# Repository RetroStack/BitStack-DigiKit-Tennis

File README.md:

# DigiKit Tennis Replica

While watching my regular YouTube channels, I saw a digital electronics kit from the 70s called Tennis from the company DigiKit, [shown on the Tech Time Traveller](https://www.youtube.com/watch?v=UqEwdttDtZE&t=2260s). This is a neat little board with a fun game that looks useful for beginners to learn digital electronics. The provided schematic had a lot of bugs and was very incorrect. 

I spent some time reverse engineering it from screenshots of the YouTube video, and the result is this board.

## Latest Files

In the "Latest" folder, you'll find the most up-to-date design files, including:

- Gerber files suitable for popular online PCB manufacturers like [PCBWay](/Latest/DigiKit_Tennis_Gerber_PCBWay.zip) and [JLCPCB](/Latest/DigiKit_Tennis_Gerber_JLCPCB.zip). Most manufacturers should be fine with either.
- A Bill of Materials (BOM) in both [CSV](/Latest/DigiKit_Tennis_BOM.csv) and [PDF](/Latest/DigiKit_Tennis_BOM.pdf) formats.
- The [full schematics](/Latest/DigiKit_Tennis_Schematics.pdf) of the board.

## How to Play

This is a simple game of Pong where the lights in the center of the board are used to indicate the path of the "ball." The goal of the game is to hit the ball back to the other player. When the player on the receiving end misses the ball, a point is given to the one sending it. The counting needs to be done independently and is not done on the board.

### How to set it up?

1. The first option to set is the toggle switch, which defines the speed of the ball. It should remain the same for the duration of the game.
2. Next, select who should serve the first ball. Switch the "Serve" slide switch to the side of the player who should serve. Then, press any "Reset" button. If the green light is not on the correct side of the person serving, switch it by pressing the "Shot" button from the other side. This will toggle the light.

### Play

When everything is set up, the serving player should press the "Shot" button on their side. (A red light and a green light should be lit on the same side!) As soon as "Shot" is pressed, a simulated "ball" is animated across the lights in the center. When the last light is reached, the other player needs to return it by pressing "Shot" in time on their side.

## Implementation

The replica has been implemented using KiCAD 8. The KiCAD project files are included in this repository.

## Bill of Materials (BOM)

Below is a list of materials needed to assemble the PCB.

| Reference               | Qty | Description        | Footprint                                                      | Datasheet                           |
| ----------------------- | --- | ------------------ | -------------------------------------------------------------- | ----------------------------------- |
| C1,C4                   | 2   | 2nF                | Capacitor_THT:C_Disc_D5.1mm_W3.2mm_P5.00mm                     |                                     |
| C2,C3                   | 2   | 33uF               | Capacitor_THT:CP_Radial_D5.0mm_P2.00mm                         |                                     |
| C5,C6,C7,C8,C9,C10      | 6   | 0.1uF              | Capacitor_THT:C_Disc_D5.1mm_W3.2mm_P5.00mm                     |                                     |
| D1,D10                  | 2   | Green              | LED_THT:LED_D5.0mm                                             |                                     |
| D2,D3,D4,D5,D6,D7,D8,D9 | 8   | Red                | LED_THT:LED_D5.0mm                                             |                                     |
| J1                      | 1   | Barrel_Jack_Switch | Connector_BarrelJack:BarrelJack_Horizontal                     |                                     |
| R1,R2,RN1               | 2   | 150                | Resistor_THT:R_Axial_DIN0207_L6.3mm_D2.5mm_P10.16mm_Horizontal |                                     |
| RN1                     | 1   | 150                | 8 Resistors; 9 pins                                            |                                     |
| R3,R4                   | 2   | 1k                 | Resistor_THT:R_Axial_DIN0207_L6.3mm_D2.5mm_P10.16mm_Horizontal |                                     |
| R5                      | 1   | 4.7k               | Resistor_THT:R_Axial_DIN0207_L6.3mm_D2.5mm_P10.16mm_Horizontal |                                     |
| SW1                     | 1   | Player A           | RetroStackLibrary:SW_SPST_Push                                 |                                     |
| SW2                     | 1   | Reset A            | RetroStackLibrary:SW_SPST_Push                                 |                                     |
| SW3                     | 1   | Serve              | RetroStackLibrary:SW_DPDT_Slide_RightAngle                     |                                     |
| SW4                     | 1   | Speed              | RetroStackLibrary:SW_SPDT_Toggle                               |                                     |
| SW5                     | 1   | Reset B            | RetroStackLibrary:SW_SPST_Push                                 |                                     |
| SW6                     | 1   | Player B           | RetroStackLibrary:SW_SPST_Push                                 |                                     |
| U1,U3,U4                | 3   | 74LS00             | Package_DIP:DIP-14_W7.62mm                                     | http://www.ti.com/lit/gpn/sn74ls00  |
| U2                      | 1   | 74LS10             | Package_DIP:DIP-14_W7.62mm                                     | http://www.ti.com/lit/gpn/sn74LS10  |
| U5,U6                   | 2   | 74LS194            | Package_DIP:DIP-16_W7.62mm                                     | http://www.ti.com/lit/gpn/sn74LS194 |

## RetroStack Libraries

To work with this KiCAD project, you'll need the RetroStack libraries for KiCAD. Please [follow this link](https://www.github.com/RetroStack/KiCAD-Libraries) to access and install these libraries.

## Support this Project

RetroStack is passionate about exploring and preserving the legacy of older computer systems. BitStack is a sub-project of RetroStack, focusing on education in digital electronics. My work involves creating detailed documentation and videos to share the knowledge. I am also dedicated to reviving these classic systems by reimplementing them and offering replacement parts at no cost. If you're keen on supporting this unique project, I invite you to visit my [Patreon page](https://www.patreon.com/RetroStack). Your support would be immensely valuable and greatly appreciated!

## License

This project is licensed under the MIT License - see the [LICENSE](LICENSE) file for details.

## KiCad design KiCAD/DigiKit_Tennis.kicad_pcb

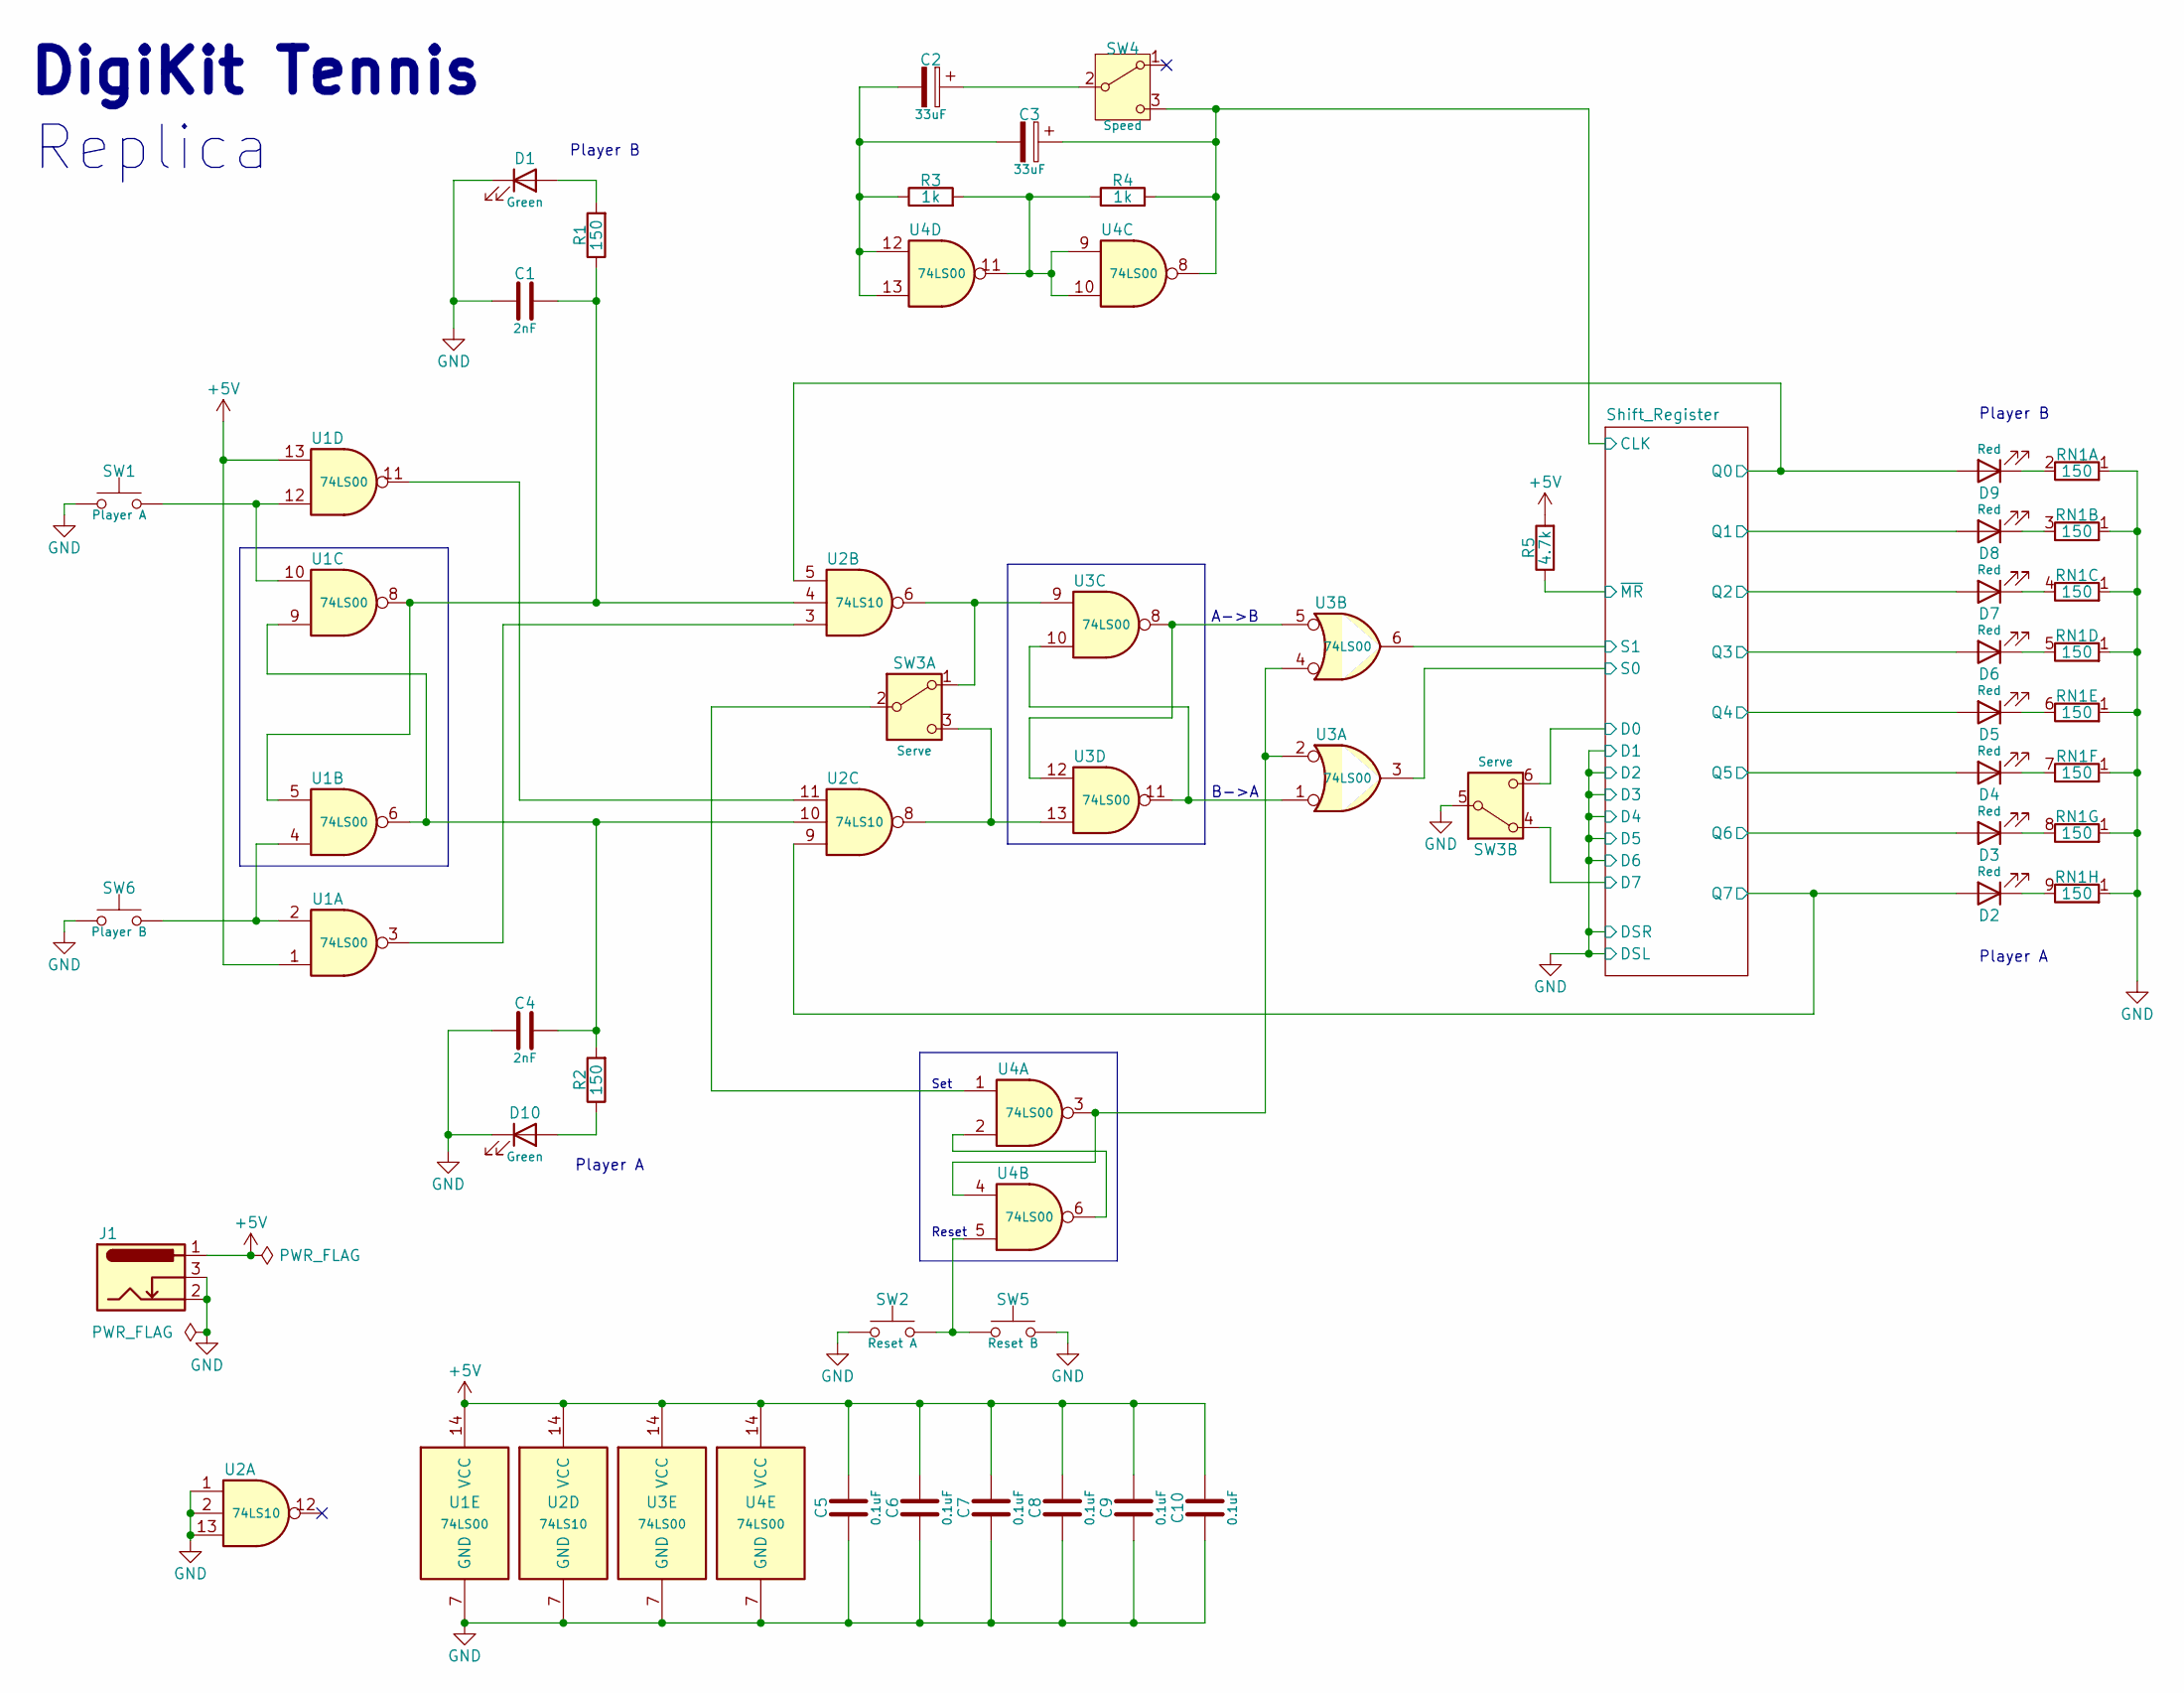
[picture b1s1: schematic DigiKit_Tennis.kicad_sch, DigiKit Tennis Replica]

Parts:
C1, C4: 2nF; C_Disc_D5.1mm_W3.2mm_P5.00mm
C2, C3: 33uF; CP_Radial_D5.0mm_P2.00mm
C5, C6, C7, C8, C9, C10: 0.1uF; C_Disc_D5.1mm_W3.2mm_P5.00mm
D1, D10: Green; LED_D5.0mm
D2, D3, D4, D5, D6, D7, D8, D9: Red; LED_D5.0mm
J1: Barrel_Jack_Switch; BarrelJack_Horizontal
R1, R2: 150; R_Axial_DIN0207_L6.3mm_D2.5mm_P10.16mm_Horizontal
R3, R4: 1k; R_Axial_DIN0207_L6.3mm_D2.5mm_P10.16mm_Horizontal
R5: 4.7k; R_Axial_DIN0207_L6.3mm_D2.5mm_P10.16mm_Horizontal
RN1: 150; R_Array_SIP9
SW1: Player A; SW_SPST_Push
SW2: Reset A; SW_SPST_Push
SW3: Serve; SW_DPDT_Slide_RightAngle
SW4: Speed; SW_SPDT_Toggle
SW5: Reset B; SW_SPST_Push
SW6: Player B; SW_SPST_Push
U1, U3, U4: 74LS00; DIP-14_W7.62mm
U2: 74LS10; DIP-14_W7.62mm

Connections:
+5V: C5.1, C6.1, C7.1, C8.1, C9.1, C10.1, J1.1, R5.2, U1.1, U1.13, U1.14 (VCC), U2.14 (VCC), U3.14 (VCC), U4.14 (VCC); also elsewhere on the board
/Shift_Register/CLK: C3.1, R4.2, SW4.3 (C), U4.8; also elsewhere on the board
/Shift_Register/D0: SW3.6 (C); also elsewhere on the board
/Shift_Register/D7: SW3.4 (A); also elsewhere on the board
/Shift_Register/Q0: D9.2 (A), U2.5; also elsewhere on the board
/Shift_Register/Q1: D8.2 (A); also elsewhere on the board
/Shift_Register/Q2: D7.2 (A); also elsewhere on the board
/Shift_Register/Q3: D6.2 (A); also elsewhere on the board
/Shift_Register/Q4: D5.2 (A); also elsewhere on the board
/Shift_Register/Q5: D4.2 (A); also elsewhere on the board
/Shift_Register/Q6: D3.2 (A); also elsewhere on the board
/Shift_Register/Q7: D2.2 (A), U2.9; also elsewhere on the board
/Shift_Register/S0: U3.3; also elsewhere on the board
/Shift_Register/S1: U3.6; also elsewhere on the board
/Shift_Register/~MR: R5.1; also elsewhere on the board
GND: C1.1, C4.1, C5.2, C6.2, C7.2, C8.2, C9.2, C10.2, D1.1 (K), D10.1 (K), J1.2, J1.3, RN1.1 (R1), SW1.1, SW2.1, SW3.5 (B), SW5.2, SW6.1, U1.7 (GND), U2.1, U2.2, U2.7 (GND), U2.13, U3.7 (GND), U4.7 (GND); also elsewhere on the board
unnamed: C1.2, R1.1, U1.5, U1.8, U2.4
unnamed: C2.2, C3.2, R3.1, U4.12, U4.13
unnamed: C4.2, R2.2, U1.6, U1.9, U2.10
unnamed: D1.2 (A), R1.2
unnamed: D2.1 (K), RN1.9 (R8.2)
unnamed: D3.1 (K), RN1.8 (R7.2)
unnamed: D4.1 (K), RN1.7 (R6.2)
unnamed: D5.1 (K), RN1.6 (R5.2)
unnamed: D6.1 (K), RN1.5 (R4.2)
unnamed: D7.1 (K), RN1.4 (R3.2)
unnamed: D8.1 (K), RN1.3 (R2.2)
unnamed: D9.1 (K), RN1.2 (R1.2)
unnamed: D10.2 (A), R2.1
unnamed: R3.2, R4.1, U4.9, U4.10, U4.11
unnamed: SW1.2, U1.10, U1.12
unnamed: SW2.2, SW5.1, U4.5
unnamed: SW3.1 (A), U2.6, U3.9
unnamed: SW3.2 (B), U4.1
unnamed: SW3.3 (C), U2.8, U3.13
unnamed: C2.1, SW4.2 (B)
unnamed: SW6.2, U1.2, U1.4
unnamed: U1.3, U2.3
unnamed: U1.11, U2.11
unnamed: U3.1, U3.10, U3.11
unnamed: U3.2, U3.4, U4.3, U4.4
unnamed: U3.5, U3.8, U3.12
unnamed: U4.2, U4.6

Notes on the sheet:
Reset
B->A
DigiKit Tennis
Replica
Player B
Player A
Set
A->B

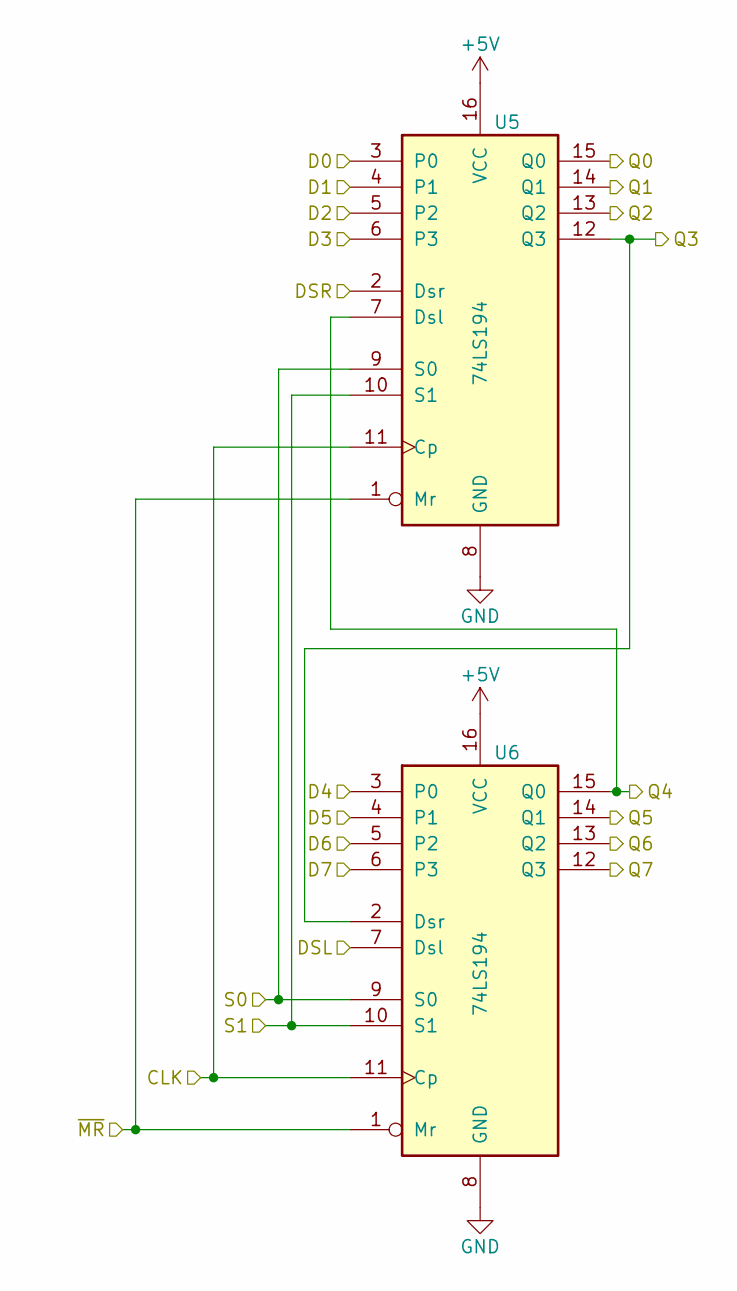
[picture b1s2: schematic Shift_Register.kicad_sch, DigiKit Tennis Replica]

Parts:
U5, U6: 74LS194; DIP-16_W7.62mm

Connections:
+5V: U5.16 (VCC), U6.16 (VCC); also elsewhere on the board
/Shift_Register/CLK: U5.11 (Cp), U6.11 (Cp); also elsewhere on the board
/Shift_Register/D0: U5.3 (P0); also elsewhere on the board
/Shift_Register/D7: U6.6 (P3); also elsewhere on the board
/Shift_Register/Q0: U5.15 (Q0); also elsewhere on the board
/Shift_Register/Q1: U5.14 (Q1); also elsewhere on the board
/Shift_Register/Q2: U5.13 (Q2); also elsewhere on the board
/Shift_Register/Q3: U5.12 (Q3), U6.2 (Dsr); also elsewhere on the board
/Shift_Register/Q4: U5.7 (Dsl), U6.15 (Q0); also elsewhere on the board
/Shift_Register/Q5: U6.14 (Q1); also elsewhere on the board
/Shift_Register/Q6: U6.13 (Q2); also elsewhere on the board
/Shift_Register/Q7: U6.12 (Q3); also elsewhere on the board
/Shift_Register/S0: U5.9 (S0), U6.9 (S0); also elsewhere on the board
/Shift_Register/S1: U5.10 (S1), U6.10 (S1); also elsewhere on the board
/Shift_Register/~MR: U5.1 (Mr), U6.1 (Mr); also elsewhere on the board
GND: U5.2 (Dsr), U5.4 (P1), U5.5 (P2), U5.6 (P3), U5.8 (GND), U6.3 (P0), U6.4 (P1), U6.5 (P2), U6.7 (Dsl), U6.8 (GND); also elsewhere on the board

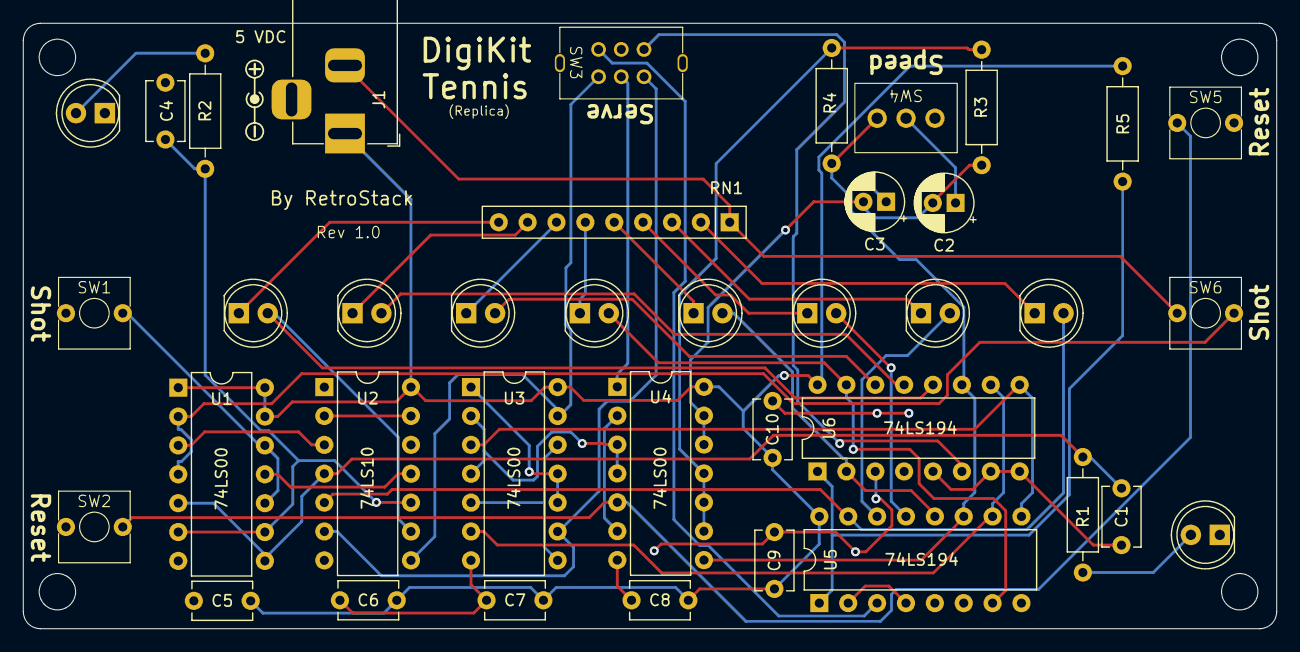
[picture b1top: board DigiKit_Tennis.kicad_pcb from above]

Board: 2 copper layers, 110.2 x 53.2 mm, 39 parts (0 on the bottom side), 43 nets.

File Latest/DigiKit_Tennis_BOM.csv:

"Reference","Value","Datasheet","Footprint","Qty"
"C1,C4","2nF","~","Capacitor_THT:C_Disc_D5.1mm_W3.2mm_P5.00mm","2"
"C2,C3","33uF","~","Capacitor_THT:CP_Radial_D5.0mm_P2.00mm","2"
"C5,C6,C7,C8,C9,C10","0.1uF","~","Capacitor_THT:C_Disc_D5.1mm_W3.2mm_P5.00mm","6"
"D1,D10","Green","~","LED_THT:LED_D5.0mm","2"
"D2,D3,D4,D5,D6,D7,D8,D9","Red","~","LED_THT:LED_D5.0mm","8"
"J1","Barrel_Jack_Switch","~","Connector_BarrelJack:BarrelJack_Horizontal","1"
"R1,R2","150","~","Resistor_THT:R_Axial_DIN0207_L6.3mm_D2.5mm_P10.16mm_Horizontal","2"
"RN1","150","~","8 Resistors; 9 pin","1"
"R3,R4","1k","~","Resistor_THT:R_Axial_DIN0207_L6.3mm_D2.5mm_P10.16mm_Horizontal","2"
"R5","4.7k","~","Resistor_THT:R_Axial_DIN0207_L6.3mm_D2.5mm_P10.16mm_Horizontal","1"
"SW1","Player A","~","RetroStackLibrary:SW_SPST_Push","1"
"SW2","Reset A","~","RetroStackLibrary:SW_SPST_Push","1"
"SW3","Serve","~","RetroStackLibrary:SW_DPDT_Slide_RightAngle","1"
"SW4","Speed","~","RetroStackLibrary:SW_SPDT_Toggle","1"
"SW5","Reset B","~","RetroStackLibrary:SW_SPST_Push","1"
"SW6","Player B","~","RetroStackLibrary:SW_SPST_Push","1"
"U1,U3,U4","74LS00","http://www.ti.com/lit/gpn/sn74ls00","Package_DIP:DIP-14_W7.62mm","3"
"U2","74LS10","http://www.ti.com/lit/gpn/sn74LS10","Package_DIP:DIP-14_W7.62mm","1"
"U5,U6","74LS194","http://www.ti.com/lit/gpn/sn74LS194","Package_DIP:DIP-16_W7.62mm","2"
